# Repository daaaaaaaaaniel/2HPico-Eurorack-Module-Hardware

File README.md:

# 2HPico-Eurorack-Module-Hardware
2HP Eurorack module based on Raspberry Pi RP2350 Pico 2

KiCad design files, BOM, Gerbers for main board and panel board and 3D printable panel.
Version 1.0 December 2025

See the repository https://github.com/rheslip/2HPico-Sketches for Pico Arduino sketches to run on it.

***General notes on the design***

Waveshare (and others) make small form factor RP2040 and RP2350 boards which make stuffing one into 2HP possible. The RP2350 has much better performance but for simple things like sequencers, ADSR, LFO etc the RP2040 should work OK. Core 0 runs the main processing loop for the UI and control,
core 1 runs the DSP and sends samples to the I2S driver. The code has an option for monitoring the performance of core 1 with a scope. If enabled you will see a pulse on GPIO 8 that indicates how much time core 1 is spending processing samples. If its high more than 100% of the time you will get audio dropouts - time to overclock or optimize your code some more!

The PT8211 16 bit stereo R2R DAC is very inexpensive and has proven so far to be quite accurate and consistent from one chip to another (provided they aren't defective - see caveats below). It has no internal antialiasing filters but it works down to DC so can be used as a CV out as well. U6 is a DC coupled antialiasing filter and it also amplifies the DAC output to +-5V eurorack levels.

***Panel PCB Build notes***

Solder the .1u cap and the RGB LED. Note pin 1 location is NOT the lead with the 45 cut on it - check the picture in the BOM. Hopefully you bought the right pinout! Note these are 5V parts but I haven't had any issues running them at 3.3v - and they are still way too bright!

Solder the jacks - note that the two bottom ones have the same GND via to save real estate

Solder the button. Glue the button cap on with a dab of superglue.

Solder the pots. You can clip the brackets near the bend to make soldering a bit easier but its not required. Make sure they are lined up vertically and horizontally before you solder the brackets to the pads. A Panavise is handy for this step.

***Main PCB Build Notes***

Solder all the 0603 Rs and Cs first

Solder diodes, R1, U3 regulator, U4 voltage reference and power connector J4. Hook it up to power and check that the 5V, -12V, +12V and -10v reference voltages are OK

Solder in all the chips, the larger caps and the trimpot RV1

The Waveshare RP2350 board cannot solder directly to the main PCB because it has components on the bottom side and must stand off a bit. You can solder .1" headers to it and solder the headers to the main PCB or solder .1" header pins in the corners and make the rest of the connections with short wires.

Power up the PCB again and check that the 5V and 3.3V rails are OK.

Solder right angle connectors J1, J2 and J3. The shorter pins solder to the main PCB as shown.

Plug the long end of the right angle connectors into the panel PCB and solder.

Clip the pins on the bottom side of the main PCB so they don't interfere with adjacent modules - a 2HP module is supposed to be only 10.16mm wide.

Solder one of the jumper pads on the bottom to select jack 2 on the panel as either DAC right channel out or a second CV/Gate input. This depends on what the module is supposed to do.

It should be ready to go. You can load up the HWtest sketch and run it to check the pots, button, inputs and DAC functions

***Trimming the DAC output***

Load up the ADSR app or mod the HWtest sketch so the I2S code is sending the value 0 to the DACs. Measure the level at the output jacks or at U6 pins 1 and 14 and trim RV1 to get as close to 0V as possible. There will probably still be a few mV difference between the channels. 
Its set up for +-5V output corresponding to -32767 and 32767 DAC values respectively (output amp inverts the DAC signals). If you want higher output levels you can mod the output stage gain but keep in mind the offset and the lowpass filters also have to be recalculated.

***Notes on the PT8211 DAC chips*** 

I bought 10 on Aliexpress and I got a couple of defective ones. Symptom was no output from either left or right DAC, just a low amplitude glitch at the opamp outputs U6 pins 1 and 14. I suggest you buy from a couple of different vendors and cross your fingers. Alternatively Sparkfun and PJRC sell PT8211 kits for a few dollars that include a PT8211 presumably from a reputable source.

***Notes on the Panel***

STL file is included for a 3D printable panel which includes a collimator that sits over the RGB LED. I glued a short piece of transparent filament inside the collimator as a light pipe - for some reason commercial acrylic light pipes are stupidly expensive. The RGB LED is very bright even on 3.3v so I cut the level back in the code. I will probably design a silkscreened FR4 panel for it at some point.

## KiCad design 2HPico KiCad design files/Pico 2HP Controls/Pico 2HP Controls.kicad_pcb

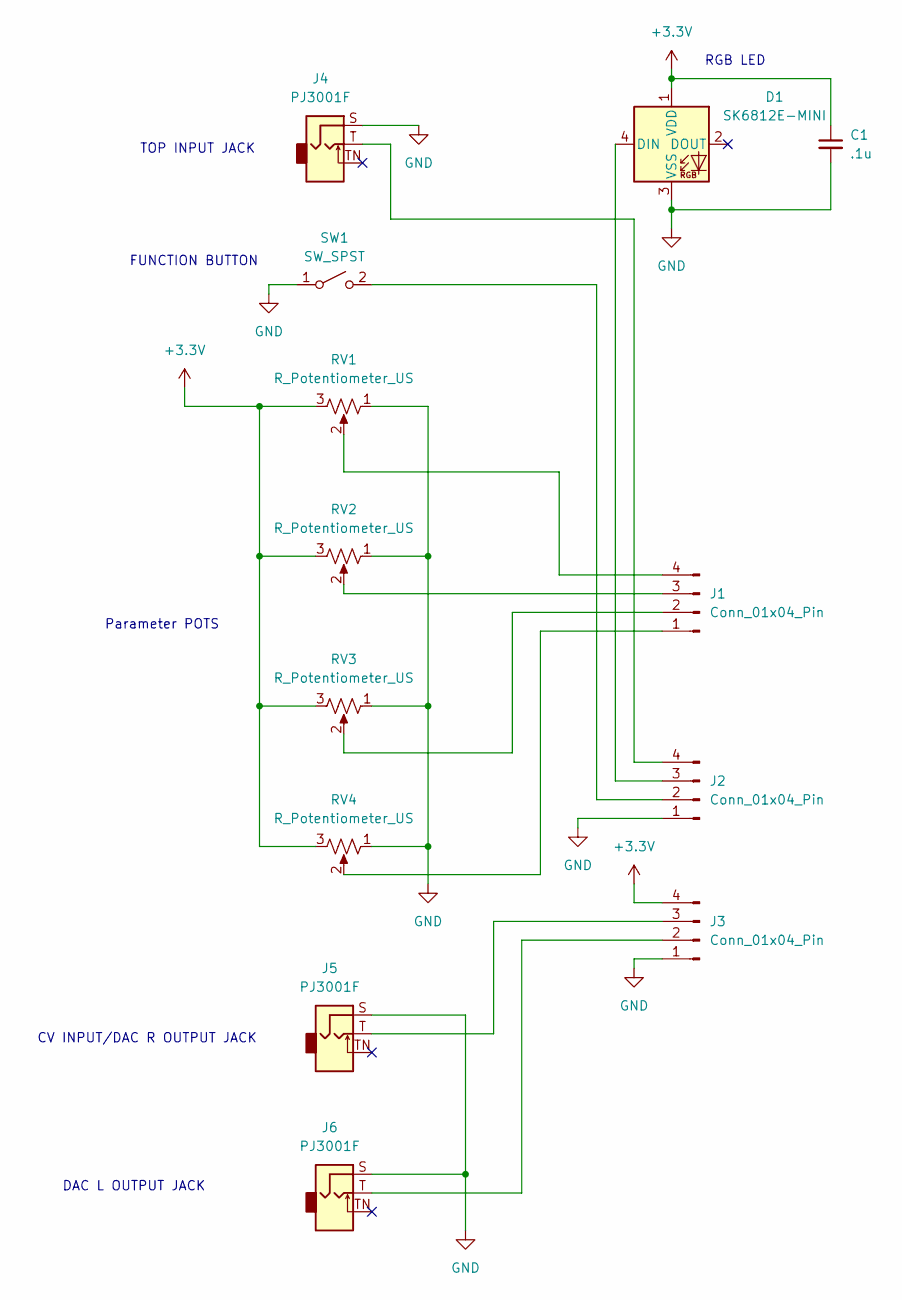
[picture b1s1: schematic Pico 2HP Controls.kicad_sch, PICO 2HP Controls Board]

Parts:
C1: .1u; C_0603_1608Metric_Pad1.08x0.95mm_HandSolder
D1: SK6812E-MINI; LED_OPSCO_SK6812_MINI-E_5.0x5.0mm_P3.1mm
J1, J2, J3: Conn_01x04_Pin; PinHeader_1x04_P2.54mm_Vertical
J4, J5, J6: PJ3001F; AudioJack_3.5mm
RV1, RV2, RV3, RV4: R_Potentiometer_US; Potentiometer_RV09_10HP
SW1: SW_SPST; SW_PUSH_6mm

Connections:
+3.3V: C1.1, D1.1 (VDD), J3.4, RV1.3, RV2.3, RV3.3, RV4.3
GND: C1.2, D1.3 (VSS), J2.1, J3.1, J4.S, J5.S, J6.S, RV1.1, RV2.1, RV3.1, RV4.1, SW1.1 (A)
unnamed: D1.4 (DIN), J2.3
unnamed: J1.1, RV4.2
unnamed: J1.2, RV3.2
unnamed: J1.3, RV2.2
unnamed: J1.4, RV1.2
unnamed: J2.2, SW1.2 (B)
unnamed: J2.4, J4.T
unnamed: J3.2, J6.T
unnamed: J3.3, J5.T

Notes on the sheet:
TOP INPUT JACK
RGB LED
FUNCTION BUTTON
DAC L OUTPUT JACK
CV INPUT/DAC R OUTPUT JACK
Parameter POTS

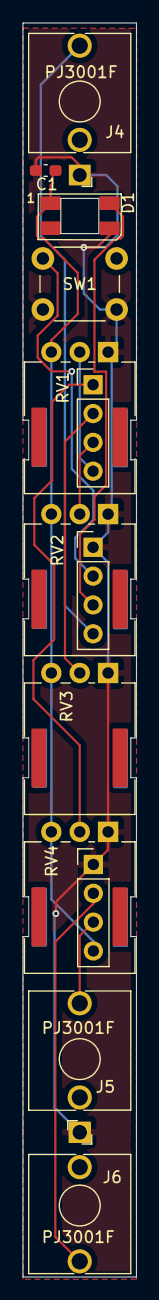
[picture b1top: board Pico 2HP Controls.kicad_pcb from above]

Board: 2 copper layers, 10.0 x 110.5 mm, 13 parts (0 on the bottom side), 11 nets.

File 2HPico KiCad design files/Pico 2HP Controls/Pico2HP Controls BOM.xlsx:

Id | Designator | Footprint | Quantity | Designation | Supplier and ref | Link | Comments
1 | J3,J1,J2 | PinHeader_1x04_P2.54mm_R/A | 0 | Conn_01x04_Pin |  |  | these are in the main board BOM - don't buy 2 sets
2 | D1 | LED_OPSCO_SK6812_MINI-E_3228SMD Reverse Mount | 1 | SK6812E-MINI | AliExpress | https://www.aliexpress.com/item/1005005193716172.html | check the pinout before you buy!
3 | J5,J4,J6 | PJ-301M AudioJack_3.5mm | 3 | PJ3001F | AliExpress | https://www.aliexpress.com/item/32919567094.html | standard eurorack jacks
4 | RV4,RV2,RV3,RV1 | Potentiometer_RV09_10HP | 4 | R_Potentiometer_US | AliExpress | https://www.aliexpress.com/item/1005003276146441.html | 10k to 100k is fine - could also use Song Huei style plastic pots with pointer 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
5 | C1 | C_0603_1608Metric_Pad1.08x0.95mm_HandSolder | 1 | .1u
6 | SW1 | SW_PUSH_6mm (13mm shaft) | 1 | SW_SPST | AliExpress | https://www.aliexpress.com/item/1005003115135192.html | 10-15mm shaft will work
7 |  | Switch Cap |  |  | AliExpress | https://www.aliexpress.com/item/32823372863.html | glue them on
8 |  | Knobs to fit pots | 4 |  | AliExpress | https://www.aliexpress.com/item/33009959086.html | do NOT use metal pots - the frame will short the board connectors

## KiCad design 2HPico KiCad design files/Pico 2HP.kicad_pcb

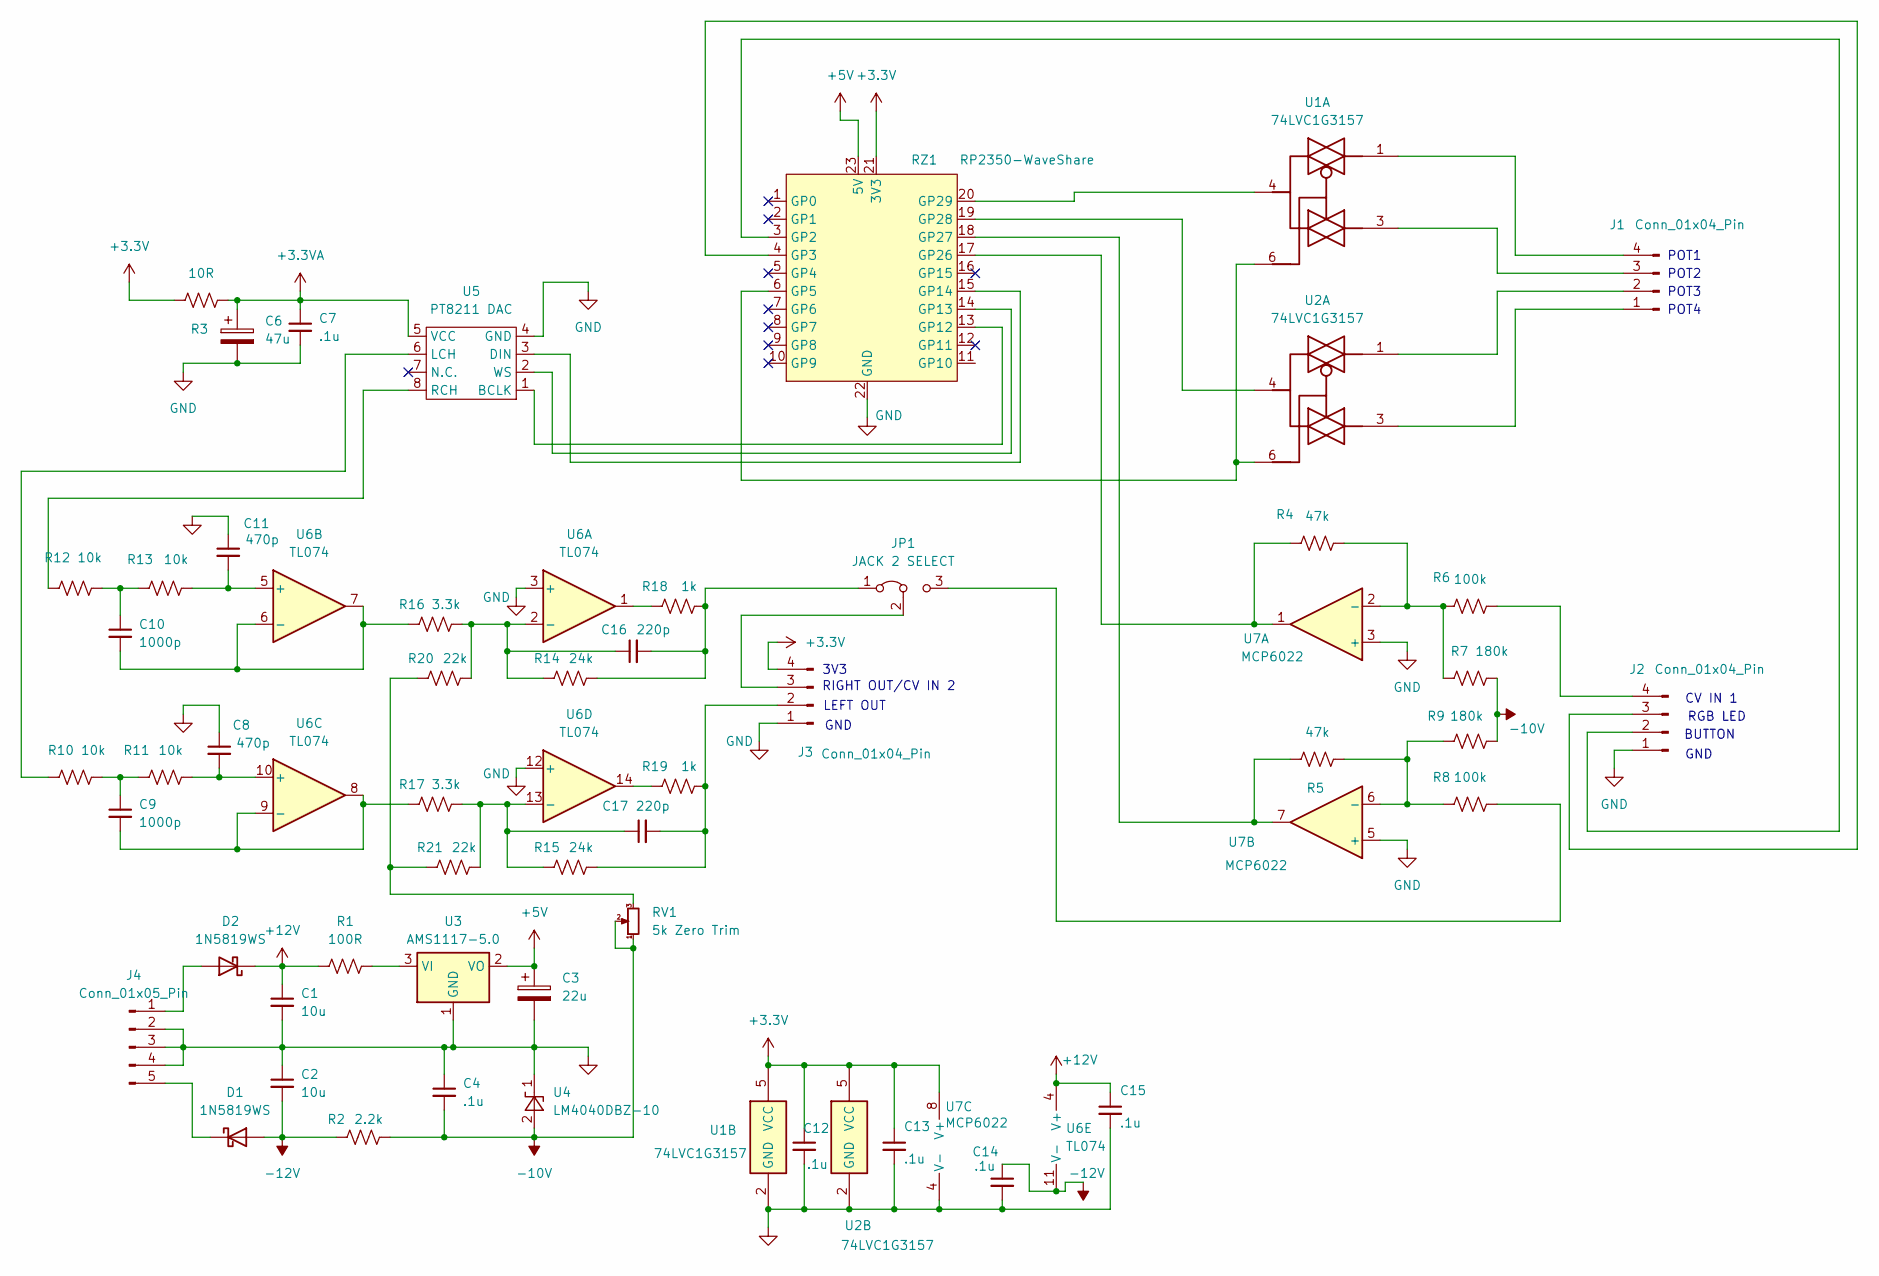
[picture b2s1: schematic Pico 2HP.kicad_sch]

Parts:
C1, C2: 10u; C_0603_1608Metric_Pad1.08x0.95mm_HandSolder
C3: 22u; CP_Elec_5x5.9
C4, C7, C12, C13, C14, C15: .1u; C_0603_1608Metric_Pad1.08x0.95mm_HandSolder
C6: 47u; CP_Elec_5x5.9
C8, C11: 470p; C_0603_1608Metric_Pad1.08x0.95mm_HandSolder
C9, C10: 1000p; C_0603_1608Metric_Pad1.08x0.95mm_HandSolder
C16, C17: 220p; C_0603_1608Metric_Pad1.08x0.95mm_HandSolder
D1, D2: 1N5819WS; D_SOD-123
J1, J2, J3: Conn_01x04_Pin; PinHeader_1x04_P2.54mm_Vertical
J4: Conn_01x05_Pin; PinHeader_1x05_P2.54mm_Vertical
JP1: JACK 2 SELECT; SolderJumper-3_P1.3mm_Open_RoundedPad1.0x1.5mm_NumberLabels
R1: 100R; R_1206_3216Metric_Pad1.30x1.75mm_HandSolder
R2: 2.2k; R_0603_1608Metric_Pad0.98x0.95mm_HandSolder
R3: 10R; R_0603_1608Metric_Pad0.98x0.95mm_HandSolder
R4, R5: 47k; R_0603_1608Metric_Pad0.98x0.95mm_HandSolder
R6, R8: 100k; R_0603_1608Metric_Pad0.98x0.95mm_HandSolder
R7, R9: 180k; R_0603_1608Metric_Pad0.98x0.95mm_HandSolder
R10, R11, R12, R13: 10k; R_0603_1608Metric_Pad0.98x0.95mm_HandSolder
R14, R15: 24k; R_0603_1608Metric_Pad0.98x0.95mm_HandSolder
R16, R17: 3.3k; R_0603_1608Metric_Pad0.98x0.95mm_HandSolder
R18, R19: 1k; R_0603_1608Metric_Pad0.98x0.95mm_HandSolder
R20, R21: 22k; R_0603_1608Metric_Pad0.98x0.95mm_HandSolder
RV1: 5k Zero Trim; Potentiometer_Bourns_TC33X_Vertical
RZ1: RP2350-WaveShare; RP2350-Waveshare
U1, U2: 74LVC1G3157; SOT-23-6
U3: AMS1117-5.0; SOT-223-3_TabPin2
U4: LM4040DBZ-10; SOT-23
U5: PT8211 DAC; SOIC-8_3.9x4.9mm_P1.27mm
U6: TL074; SOIC-14_3.9x8.7mm_P1.27mm
U7: MCP6022; SOIC-8_3.9x4.9mm_P1.27mm

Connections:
+3.3V: C12.1, C13.1, J3.4, R3.1, RZ1.21 (3V3), U1.5 (VCC), U2.5 (VCC), U7.8 (V+)
+3.3VA: C6.1, C7.1, R3.2, U5.5 (VCC)
+5V: C3.1, RZ1.23 (5V), U3.2 (VO)
+12V: C1.1, C15.1, D2.1 (K), R1.1, U6.4 (V+)
-10V: C4.2, R2.2, R7.2, R9.2, RV1.1, RV1.2, U4.2 (A)
-12V: C2.2, C14.1, D1.2 (A), R2.1, U6.11 (V-)
GND: C1.2, C2.1, C3.2, C4.1, C6.2, C7.2, C8.1, C11.1, C12.2, C13.2, C14.2, C15.2, J2.1, J3.1, J4.2, J4.3, J4.4, RZ1.22 (GND), U1.2 (GND), U2.2 (GND), U3.1 (GND), U4.1 (K), U5.4 (GND), U6.3 (+), U6.12 (+), U7.3 (+), U7.4 (V-), U7.5 (+)
unnamed: C9.1, R10.2, R11.1
unnamed: C10.1, R12.2, R13.1
unnamed: D1.1 (K), J4.5
unnamed: D2.2 (A), J4.1
unnamed: J1.1, U2.3
unnamed: J1.2, U2.1
unnamed: J1.3, U1.3
unnamed: J1.4, U1.1
unnamed: J2.2, RZ1.3 (GP2)
unnamed: J2.3, RZ1.4 (GP3)
unnamed: J2.4, R6.2
unnamed: C17.2, J3.2, R15.2, R19.2
unnamed: J3.3, JP1.2 (C)
unnamed: C16.2, JP1.1 (A), R14.2, R18.2
unnamed: JP1.3 (B), R8.2
unnamed: R18.1, U6.1
unnamed: R19.1, U6.14
unnamed: R20.1, R21.1, RV1.3
unnamed: RZ1.6 (GP5), U1.6, U2.6
unnamed: RZ1.13 (GP12), U5.1 (BCLK)
unnamed: RZ1.14 (GP13), U5.2 (WS)
unnamed: RZ1.15 (GP14), U5.3 (DIN)
unnamed: R4.1, RZ1.17 (GP26), U7.1
unnamed: R5.1, RZ1.18 (GP27), U7.7
unnamed: RZ1.19 (GP28), U2.4
unnamed: RZ1.20 (GP29), U1.4
unnamed: R1.2, U3.3 (VI)
unnamed: R10.1, U5.6 (LCH)
unnamed: R12.1, U5.8 (RCH)
unnamed: C16.1, R14.1, R16.2, R20.2, U6.2 (-)
unnamed: C11.2, R13.2, U6.5 (+)
unnamed: C10.2, R16.1, U6.6 (-), U6.7
unnamed: C8.2, R11.2, U6.10 (+)
unnamed: C9.2, R17.1, U6.8, U6.9 (-)
unnamed: C17.1, R15.1, R17.2, R21.2, U6.13 (-)
unnamed: R4.2, R6.1, R7.1, U7.2 (-)
unnamed: R5.2, R8.1, R9.1, U7.6 (-)

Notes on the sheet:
CV IN 1
GND
POT2
POT1
LEFT OUT
POT3
POT4
RGB LED
BUTTON
RIGHT OUT/CV IN 2
3V3

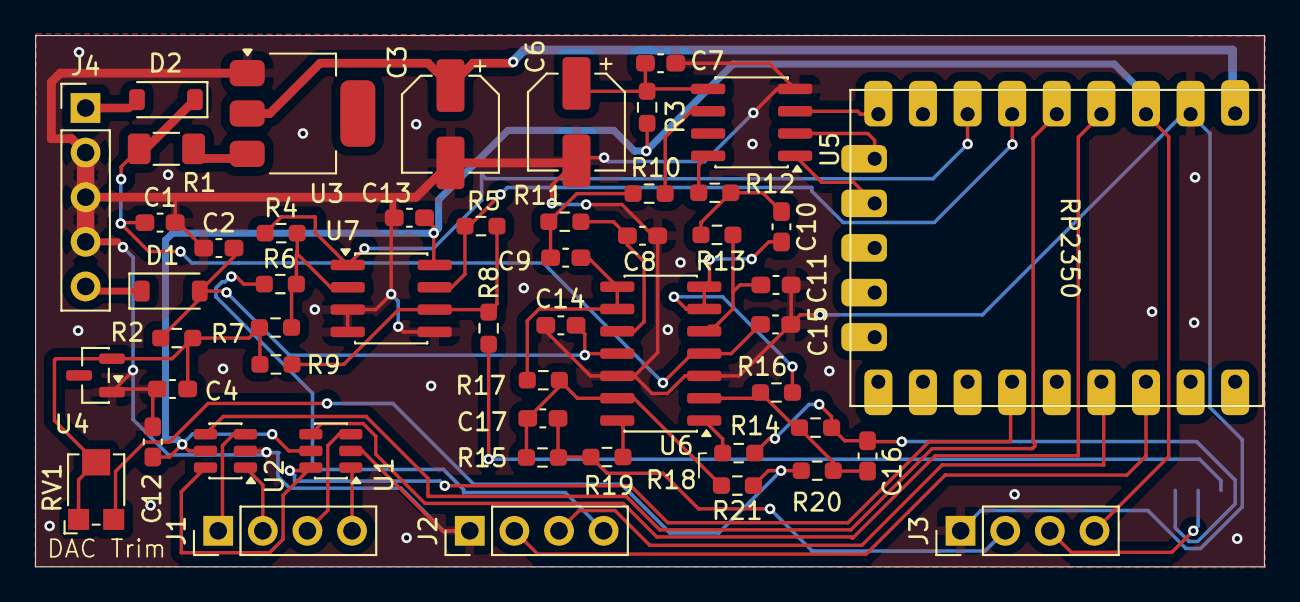
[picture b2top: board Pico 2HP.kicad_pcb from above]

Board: 2 copper layers, 70.0 x 30.3 mm, 53 parts (1 on the bottom side), 44 nets.

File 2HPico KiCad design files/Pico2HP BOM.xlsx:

Id | Designator | Footprint | Quantity | Designation | Supplier and ref | Link | Comments
1 | U7 | SOIC-8_3.9x4.9mm_P1.27mm | 1 | MCP6022
2 | R2 | R_0603_1608Metric_Pad0.98x0.95mm_HandSolder | 1 | 2.2k
3 | R14,R15 | R_0603_1608Metric_Pad0.98x0.95mm_HandSolder | 2 | 24k 1%
4 | J2,J1,J3 | PinHeader_1x04_P2.54mm_R/A | 3 | Conn_01x04_Pin |  |  | Connects PCB to panel - 90 degree mount
5 | C6 | CP_Elec_5x5.9 | 1 | 47u |  |  | value not critical 22-100u, 6V rating or higher
6 | U6 | SOIC-14_3.9x8.7mm_P1.27mm | 1 | TL074
7 | R19,R18 | R_0603_1608Metric_Pad0.98x0.95mm_HandSolder | 2 | 1k 1%
8 | C15,C12,C13,C7,C14,C4 | C_0603_1608Metric_Pad1.08x0.95mm_HandSolder | 6 | .1u
9 | R16,R17 | R_0603_1608Metric_Pad0.98x0.95mm_HandSolder | 2 | 3.3k 1%
10 | R21,R20 | R_0603_1608Metric_Pad0.98x0.95mm_HandSolder | 2 | 18k 1%
11 | R13,R10,R12,R11 | R_0603_1608Metric_Pad0.98x0.95mm_HandSolder | 4 | 10k
12 | C16,C17 | C_0603_1608Metric_Pad1.08x0.95mm_HandSolder | 2 | 220p
13 | C11,C8 | C_0603_1608Metric_Pad1.08x0.95mm_HandSolder | 2 | 470p
14 | R1 | R_1206_3216Metric_Pad1.30x1.75mm_HandSolder | 1 | 100R
15 | R4,R5 | R_0603_1608Metric_Pad0.98x0.95mm_HandSolder | 2 | 47k 1%
16 | C3 | CP_Elec_5x5.9 | 1 | 22u 16V
17 | RV1 | Potentiometer_Bourns_TC33X 3mm | 1 | 5k Zero Trim |  |  | pads will fit most small SMT trimpots
18 | U4 | SOT-23 | 1 | LM4040DBZ-10
19 | R9,R7 | R_0603_1608Metric_Pad0.98x0.95mm_HandSolder | 2 | 180k 1%
20 | U1,U2 | SOT-23-6 | 2 | 74LVC1G3157 |  |  | analog switch
21 | C2,C1 | C_0603_1608Metric_Pad1.08x0.95mm_HandSolder | 2 | 10u 16V |  |  | 0603 ceramic
22 | U5 | SOIC-8_3.9x4.9mm_P1.27mm | 1 | PT8211 DAC | Aliexpress | lots of suppliers - roll the dice | Don't buy semis from Aliexpress unless you have to -fake and defective parts ar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
23 | C10,C9 | C_0603_1608Metric_Pad1.08x0.95mm_HandSolder | 2 | 1000p
24 | D2,D1 | D_SOD-123 | 2 | 1N5819WS
25 | J4 | PinHeader_1x05_P2.54mm_R/A | 1 | Conn_01x05_Pin |  |  | Power connector - 90 degree mount
26 | R8,R6 | R_0603_1608Metric_Pad0.98x0.95mm_HandSolder | 2 | 100k 1%
27 | R3 | R_0603_1608Metric_Pad0.98x0.95mm_HandSolder | 1 | 10R
28 | RZ1 | RP2350-Waveshare - make sure its the right pinout | 1 | RP2350 | Amazon or AliExpress | https://www.amazon.ca/RP2350-Zero-Development-Dual-Architect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
29 | U3 | SOT-223-3_TabPin2 | 1 | AMS1117-5.0 |  |  | 5V regulator - most 1117 type regulators have the same pinout
30 |  | PinHeader_1x09_P2.54mm | 2 |  |  |  | Mounts RP2350 module to PCB
31 |  | PinHeader_1x05_P2.54mm | 1 |  |  |  | Mounts RP2350 module to PCB

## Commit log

2025-12-19 Initial Commit
    Initial commit
2025-12-20 updated readme
    updated readme
2025-12-31 Correct MCP6022 purchase link
    Previously, the purchase link for the MCP6022 erroneously links to a different component (MCP6002). Fixed.
